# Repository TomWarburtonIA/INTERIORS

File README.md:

# INTERIORS
Anything to do with the INTERIORS facility at the University of York

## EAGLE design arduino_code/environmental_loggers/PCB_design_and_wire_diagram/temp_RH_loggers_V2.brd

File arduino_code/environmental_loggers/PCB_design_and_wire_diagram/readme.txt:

This subdirectory contains all the PCB designs and wiring diagrams for the environment loggers (for logging temperature and relative humidity from a Met One 085a probe)

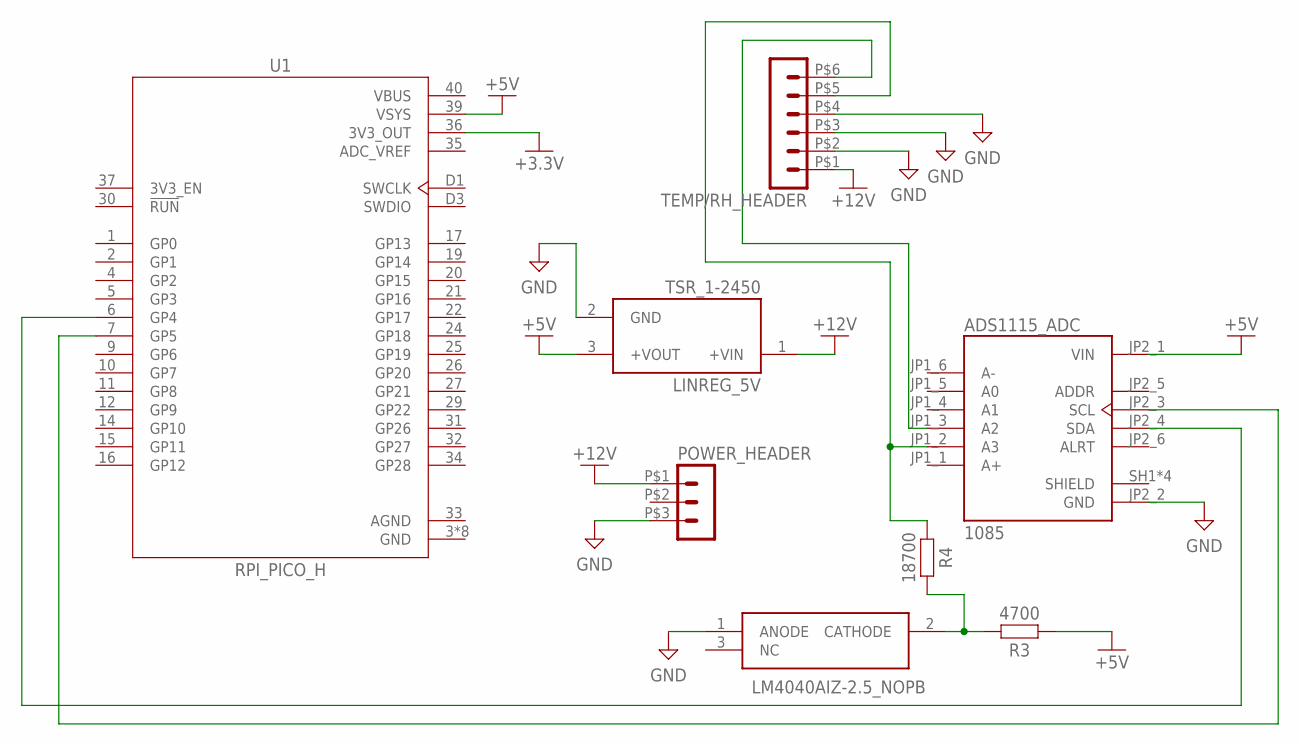
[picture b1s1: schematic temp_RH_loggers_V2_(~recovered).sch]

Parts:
ADS1115_ADC: 1085; MODULE_1085
IC1: LM4040AIZ-2.5_NOPB; LP0003A
LINREG_5V: TSR_1-2450; CONV_TSR_1-2450
POWER_HEADER: HEADER_POS3_43650-0315; 43650-0315
R3: 4700; RESAD1176W63L850D250B
R4: 18700; RESAD1176W63L850D250B
TEMP/RH_HEADER: HEADER_POS6_43045-0600; 43045-0600
U1: RPI_PICO_H; PI_PICO_H

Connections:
+3.3V: U1.36 (3V3_OUT)
+5V: ADS1115_ADC.JP2_1 (VIN), LINREG_5V.3 (+VOUT), R3.1, U1.39 (VSYS)
+12V: LINREG_5V.1 (+VIN), POWER_HEADER.P$1 (1), TEMP/RH_HEADER.P$1 (1)
ADC_VREF: U1.35 (ADC_VREF)
AGND: U1.33 (AGND)
GND: ADS1115_ADC.JP2_2 (GND), IC1.1 (ANODE), LINREG_5V.2 (GND), POWER_HEADER.P$3 (3), TEMP/RH_HEADER.P$2 (2), TEMP/RH_HEADER.P$3 (3), TEMP/RH_HEADER.P$4 (4), U1.3 (GND), U1.8 (GND), U1.13 (GND), U1.18 (GND), U1.23 (GND), U1.28 (GND), U1.38 (GND), U1.D2 (GND)
unnamed: IC1.2 (CATHODE), R3.2, R4.2
unnamed: ADS1115_ADC.JP1_2 (A3), R4.1, TEMP/RH_HEADER.P$5 (5)
unnamed: ADS1115_ADC.JP1_3 (A2), TEMP/RH_HEADER.P$6 (6)
unnamed: ADS1115_ADC.JP2_4 (SDA), U1.6 (GP4)
unnamed: ADS1115_ADC.JP2_3 (SCL), U1.7 (GP5)
VBUS: U1.40 (VBUS)

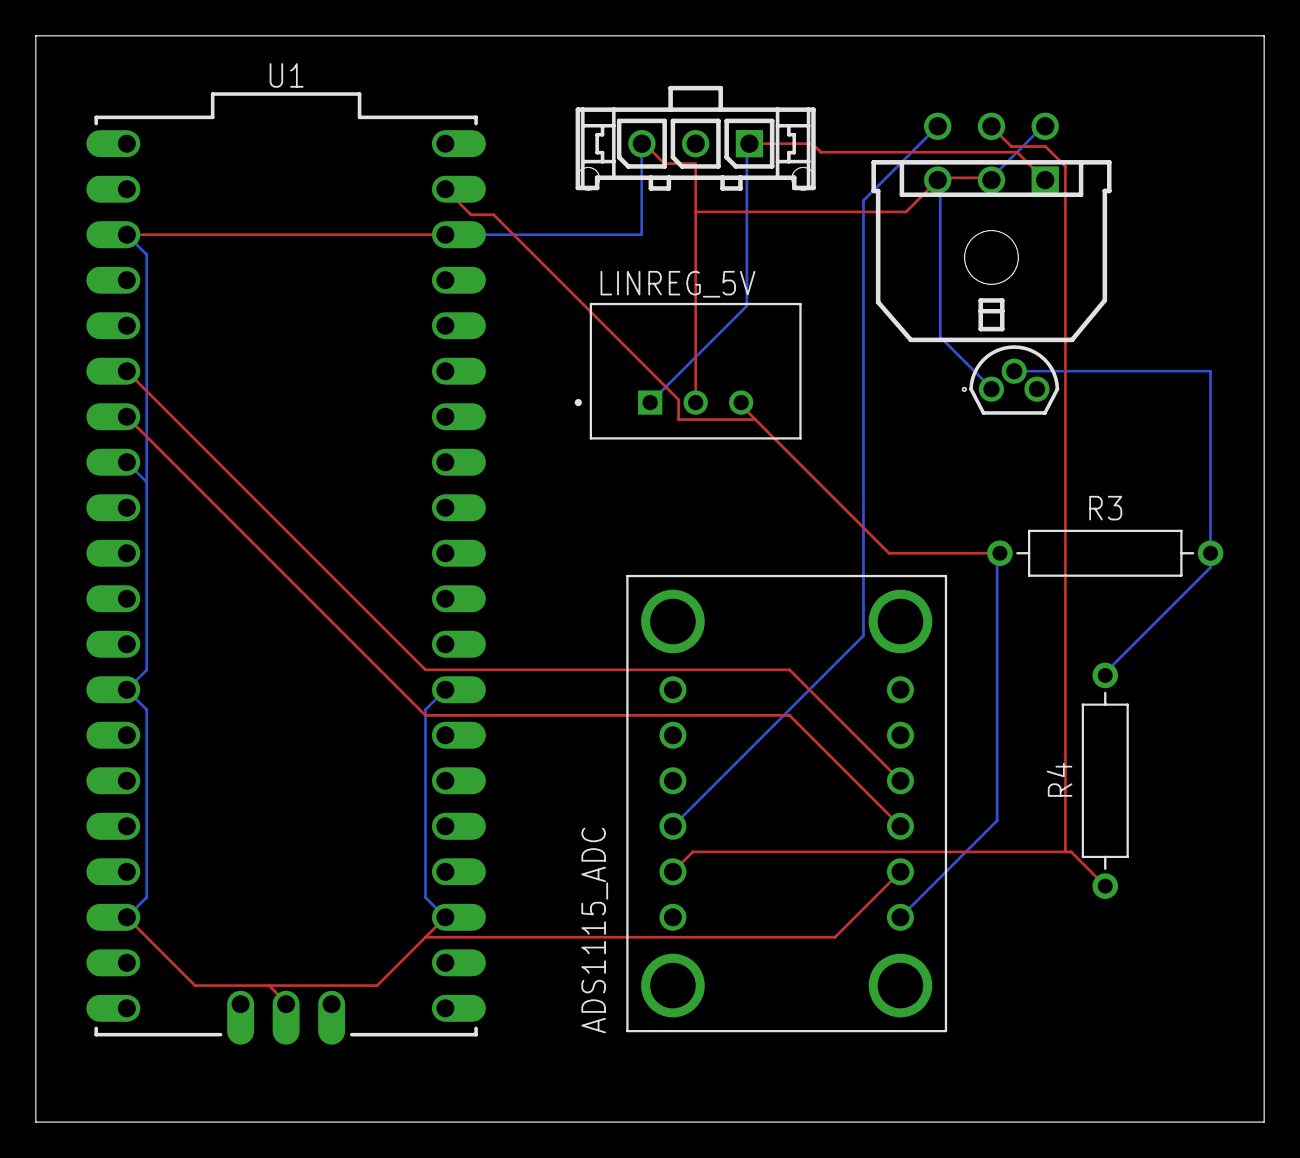
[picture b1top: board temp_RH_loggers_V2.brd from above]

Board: 2 copper layers, 68.6 x 60.6 mm, 8 parts (0 on the bottom side), 8 nets.

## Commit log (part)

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2025-08-08 Create molex_microfit_openSCAD_cutout_template.scad
    Template for creating Molex Microfit templated in OpenSCAD. Resulting shape can be exported as .STL and imported into a CAD program to create a hole in the shape of the template.
2026-01-09 Create readme for Arduino environmental
    Add initial readme for environmental loggers
2026-01-09 Refactor comments for network config and measurements
    Updated comments for clarity and consistency in the code.
2026-01-09 Update readme.txt
    Updated readme to provide detailed instructions for using the solenoid control code with DAQFactory.
2026-01-14 Add initial readme.txt with placeholder text
2026-01-14 commsSequencing.txt
2026-01-16 Include instrumentClass
    Added instructions for integrating Arduino with DAQFactory.
2026-01-18 update
    Updated readme.txt to provide detailed communication instructions for the Teledyne T701H.
2026-01-28 including T and RH calculations
